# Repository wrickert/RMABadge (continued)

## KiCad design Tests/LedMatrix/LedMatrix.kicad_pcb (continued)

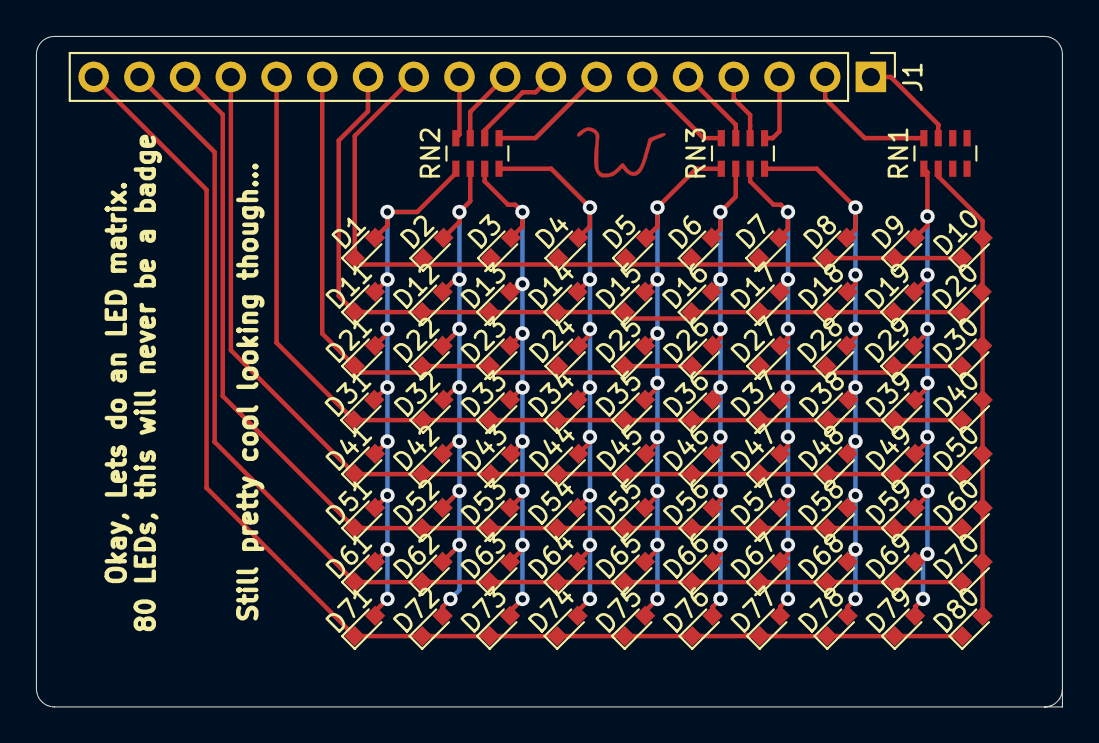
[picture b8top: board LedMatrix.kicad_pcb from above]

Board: 2 copper layers, 57.0 x 37.2 mm, 85 parts (0 on the bottom side), 28 nets.

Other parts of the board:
Ref**: Val**; W
